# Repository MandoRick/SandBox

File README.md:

# SandBox
my Sandbox

this is a place where i keep my garbage code so please ignore it

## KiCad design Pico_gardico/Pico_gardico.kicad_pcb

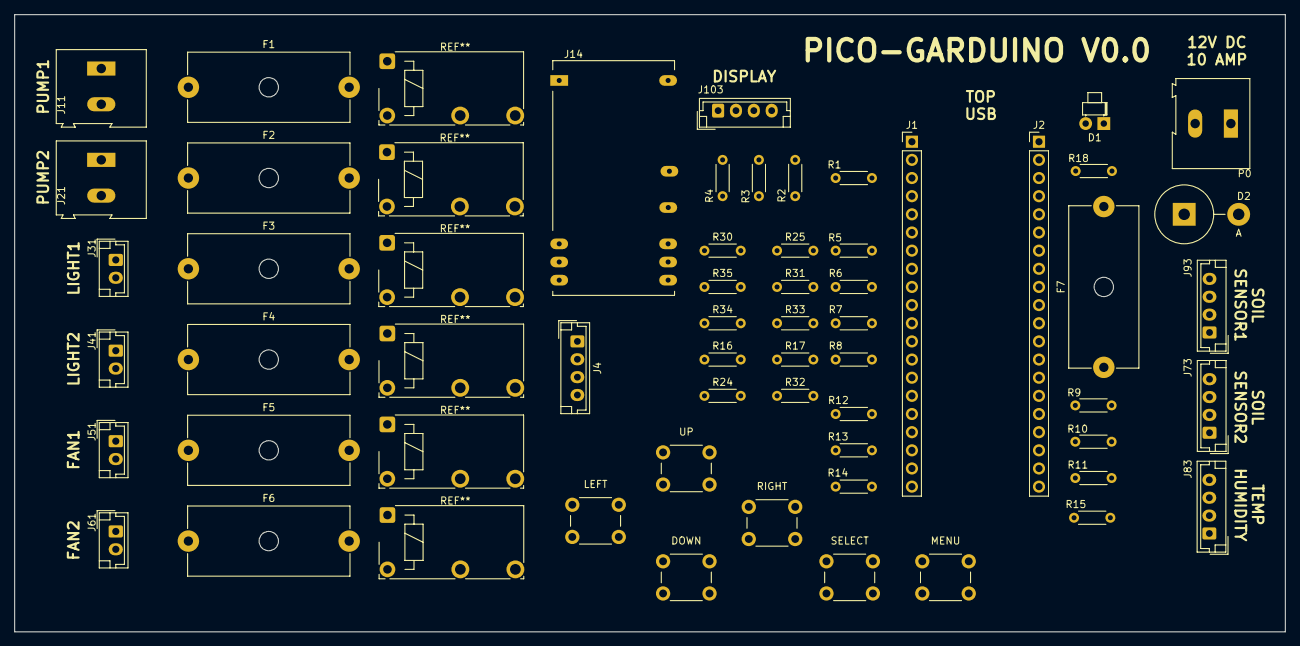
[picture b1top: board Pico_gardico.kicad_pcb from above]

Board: 2 copper layers, 177.8 x 86.4 mm, 56 parts (0 on the bottom side), 32 nets, no tracks yet.

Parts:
D1: PWR_LED; LED_D1.8mm_W1.8mm_H2.4mm_Horizontal_O1.27mm_Z1.6mm
D2: D_Schottky; D_5KPW_P7.62mm_Vertical_AnodeUp
DOWN: SW_Push; SW_PUSH_6mm
F1, F2, F3, F4, F5, F6, F7: Fuse; Fuseholder_Cylinder-5x20mm_Schurter_0031_8201_Horizontal_Op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
J1, J2: PICO; PinHeader_1x20_P2.54mm_Vertical
J4: RTC; JST_EH_B4B-EH-A_1x04_P2.50mm_Vertical
J11: Pump; TerminalBlock_Altech_AK300-2_P5.00mm
J14: BuckIN; Converter_DCDC_Bothhand_CFUDxxxx_THT
J21: Pump2; TerminalBlock_Altech_AK300-2_P5.00mm
J31: Light; JST_EH_B2B-EH-A_1x02_P2.50mm_Vertical
J41: Light2; JST_EH_B2B-EH-A_1x02_P2.50mm_Vertical
J51: Fan; JST_EH_B2B-EH-A_1x02_P2.50mm_Vertical
J61: Fan2; JST_EH_B2B-EH-A_1x02_P2.50mm_Vertical
J73, J93: Soil Moisture; JST_EH_B4B-EH-A_1x04_P2.50mm_Vertical
J83: DHT11; JST_EH_B4B-EH-A_1x04_P2.50mm_Vertical
J103: Display; JST_EH_B4B-EH-A_1x04_P2.50mm_Vertical
LEFT: SW_Push; SW_PUSH_6mm
MENU: SW_Push; SW_PUSH_6mm
P0: 12V10A; TerminalBlock_Altech_AK300-2_P5.00mm
R1, R2, R5, R6, R7, R8, R9, R10, R11, R12, R13, R14, R15, R16, R17: 33R; R_Axial_DIN0204_L3.6mm_D1.6mm_P5.08mm_Horizontal
R3, R4, R24, R25, R30, R31, R32, R33, R34, R35: 10k; R_Axial_DIN0204_L3.6mm_D1.6mm_P5.08mm_Horizontal
R18: 1K; R_Axial_DIN0204_L3.6mm_D1.6mm_P5.08mm_Horizontal
RIGHT: SW_Push; SW_PUSH_6mm
SELECT: SW_Push; SW_PUSH_6mm
UP: SW_Push; SW_PUSH_6mm

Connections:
3.3V: DOWN.1, LEFT.1, MENU.1, RIGHT.1, SELECT.1, UP.1
+3V3: R3.1, R4.1, R24.1, R25.1
BUTTON 1: R30.1, UP.2
BUTTON 2: LEFT.2, R31.1
BUTTON 3: MENU.2, R32.1
BUTTON 4: R33.1, RIGHT.2
BUTTON 5: DOWN.2, J1.4 (GP2), R34.1
BUTTON 6: J1.5 (GP3), R35.1, SELECT.2
GND: D1.1 (K), D2.1 (K), J1.3 (GND), J1.8 (GND), J1.13 (GND), J1.18 (GND), J4.2, J11.2, J21.2, J31.2, J41.2, J51.2, J61.2, J73.2, J83.4, J93.2, J103.2, P0.1, R30.2, R31.2, R32.2, R33.2, R34.2, R35.2
unnamed: D1.2 (A), R18.2
unnamed: D2.2 (A), F7.2, P0.2
unnamed: J1.6 (GP4), R16.2
unnamed: J1.7 (GP5), R17.2
unnamed: J1.9 (GP6), R1.2
unnamed: J1.10 (GP7), R2.2
unnamed: J1.14 (GP10), R5.2
unnamed: J1.15 (GP11), R6.2
unnamed: J1.16 (GP12), R7.2
unnamed: J1.17 (GP13), R12.2
unnamed: J1.19 (GP14), R13.2
unnamed: J1.20 (GP15), R14.2
unnamed: J4.3, R17.1, R25.2
unnamed: J4.4, R16.1, R24.2
unnamed: J83.2, R15.2
unnamed: J93.3, R9.2
unnamed: J93.4, R8.2
unnamed: J103.3, R2.1, R4.2
unnamed: J103.4, R1.1, R3.2
unnamed: J73.4, R10.2
unnamed: J73.3, R11.2
VEXT: J4.1, J73.1, J83.1, J93.1, J103.1
VEXT12: F1.2, F2.2, F3.2, F4.2, F5.2, F6.2, F7.1, J14.1, R18.1

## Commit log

2021-07-21 WeirdMulticore
    WeirdMulticore
